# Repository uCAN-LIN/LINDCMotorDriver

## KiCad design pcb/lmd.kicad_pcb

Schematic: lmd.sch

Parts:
C1: 220p; C_0603
C2: 10u; C_1206
C3: 10u; CP_Elec_3x5.3
C4, C6, C7: 100n; C_0603
C8: 10n; C_0603
C9, C10: 4,7u; C_0805
D1: D_Small; D_SOT-23_ANK
J1: Conn_01x05; DBG_CONN
J2, J8: Conn_01x04; Pin_Header_Straight_1x04_Pitch1.27mm
J3: Conn_01x03; TerminalBlock_Altech_AK300-3_P5.00mm
P1: CONN_01X04; Pin_Header_Straight_1x04_Pitch2.54mm
R1, R7: 10k; R_0603
R5, R6: 1,2k; R_0603
R8: 0; R_0603
U1: TLE493D/TLV493; TSOP-6_1.65x3.05mm_Pitch0.95mm
U2: TJA1028; SOIC-8_3.9x4.9mm_Pitch1.27mm
U3: POLOLU_DRV8825/DRV8801; POLOLU_DRV8825_DRV8801
U4: PIC16(L)F15323/PIC16(L)F15325; TSSOP-14_4.4x5mm_Pitch0.65mm

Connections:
+3V3: C4.1, C6.1, C7.1, C8.1, C10.1, J1.2, J2.3, J8.3, R1.1, R5.2, R6.2, R7.2, U1.6, U2.2, U2.8, U4.1, U4.5
+12P: C2.1, C3.1, D1.2, J3.3, U3.16 (nc/VMOT)
DRV_DIR: J1.4, U3.8 (DIR/nc), U4.13
DRV_MS1: U3.2 (MS1/GND), U4.8
DRV_MS2: U3.3 (MS2/PWM), U4.9
DRV_MS3: U3.4 (MS3/DIR), U4.10
DRV_STEP: U3.7 (STEP/VDD), U4.11
DRV_nENABLE: J1.1, U3.1 (nEnable/nc), U4.4
DRV_nFAULT: R8.2, U3.10 (nFAULT)
GND: C1.2, C2.2, C3.2, C4.2, C6.2, C7.2, C8.2, C9.1, C10.2, J1.3, J2.4, J3.2, J8.4, U1.2, U1.3, U1.5, U2.3, U3.9 (nc/GND), U3.15 (GND), U4.14
I2C_SCL: J2.2, J8.2, R5.1, U1.1, U4.6
I2C_SDA: J2.1, J8.1, R6.1, U1.4, U4.7
ICSPCLK: J1.5, R8.1, U4.12
LIN_RX: R7.1, U2.5, U4.3
LIN_TX: U2.6, U4.2
unnamed: C1.1, J3.1, U2.4
unnamed: C9.2, D1.1, U2.1
unnamed: P1.1, U3.11 (CS/A2)
unnamed: P1.2, U3.12 (VMM/A1)
unnamed: P1.3, U3.13 (-O/B1)
unnamed: P1.4, U3.14 (+O/B2)
unnamed: R1.2, U3.5 (nRESET/nSLD), U3.6 (nSLEEP/BRK)

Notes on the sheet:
I2C

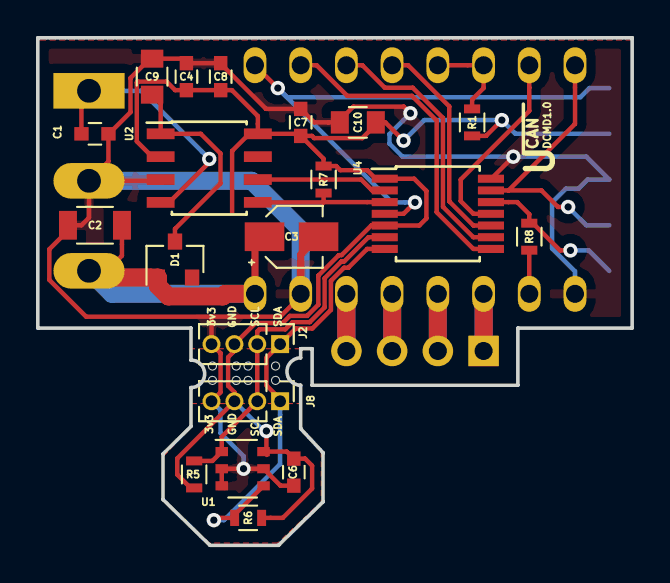
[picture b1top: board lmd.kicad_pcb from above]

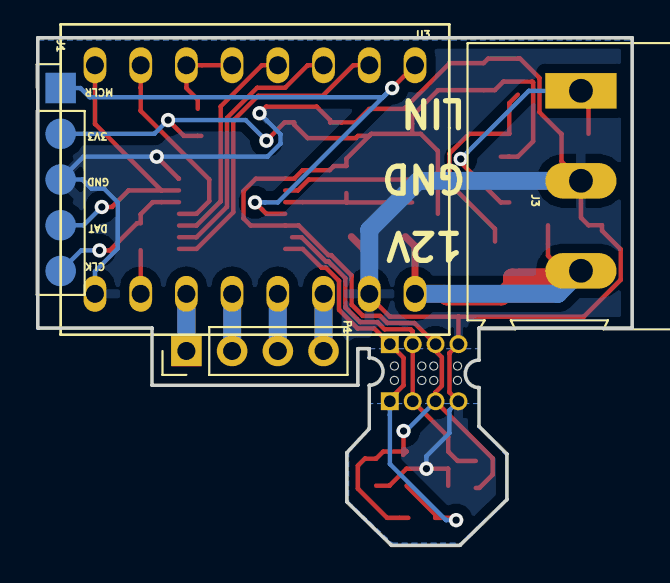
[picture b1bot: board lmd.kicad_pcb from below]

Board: 2 copper layers, 33.0 x 28.2 mm, 32 parts (4 on the bottom side), 22 nets.

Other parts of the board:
J6, J6#2, J6#3, J6#4, J6#5, J6#6, J6#7, J6#8: Conn_01x04; hole

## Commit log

2018-04-19 Inital schematic
2018-04-24 Layout fix
2018-05-21 PCB release
2018-05-22 Embedded add
2018-05-28 DRV use
